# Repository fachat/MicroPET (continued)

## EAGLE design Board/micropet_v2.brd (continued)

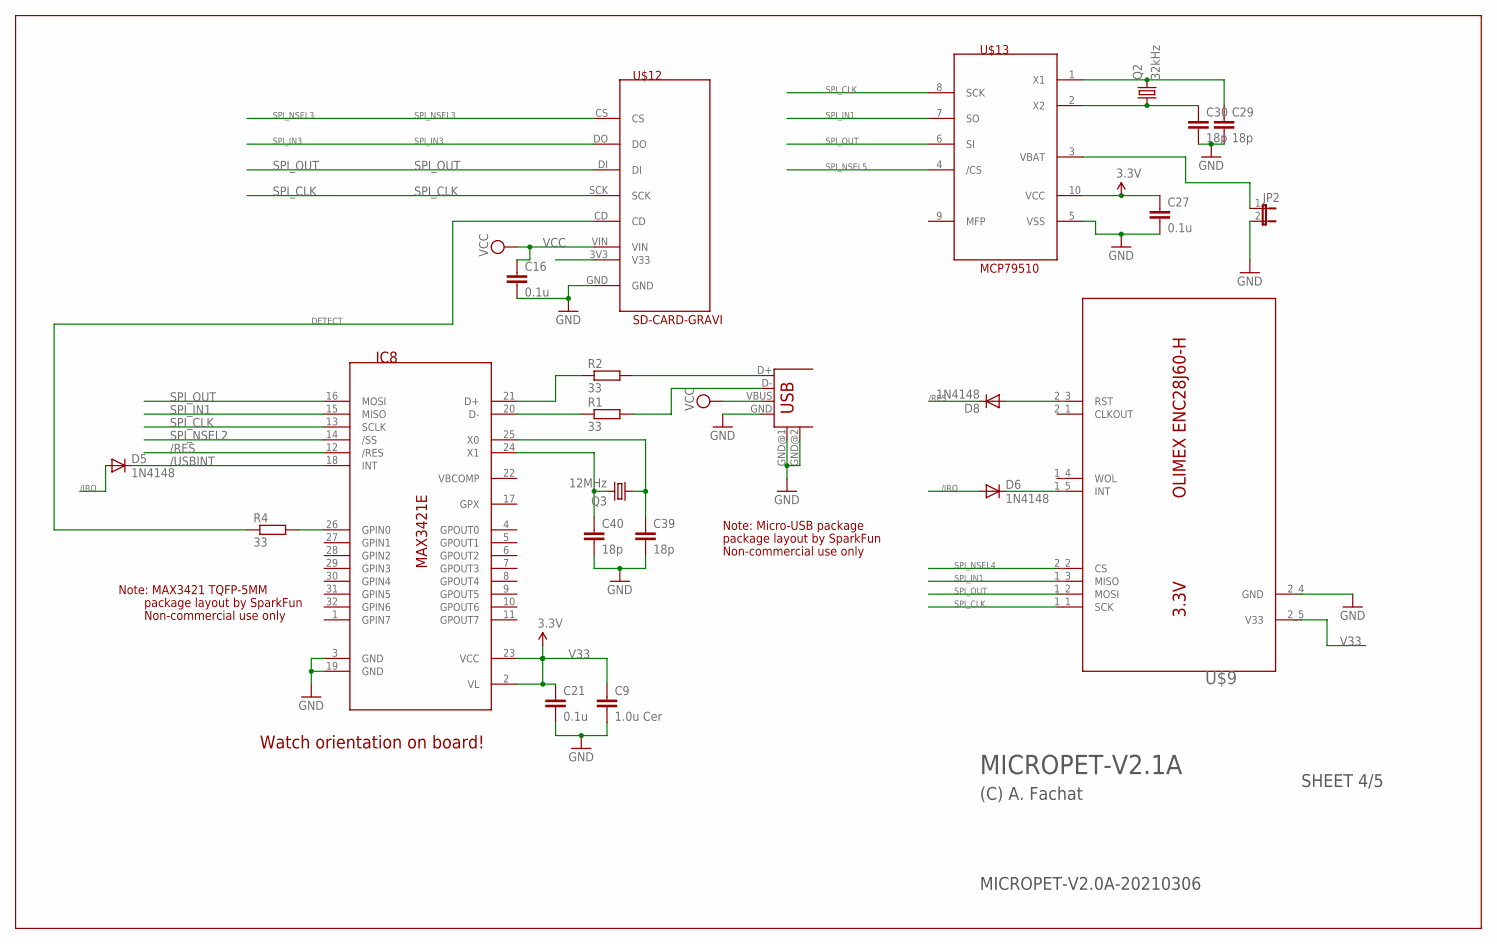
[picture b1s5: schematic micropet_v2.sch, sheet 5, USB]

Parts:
C9: 1.0u Cer; C0603
C16, C21, C27: 0.1u; C0603
C29, C30, C39, C40: 18p; C0603
D5, D6, D8: 1N4148; D-5
IC8: MAX3421E; TQFP32-5MM
JP2: JP1E; JP1
Q2: 32kHz; TC26H
Q3: 12MHz; HC49/S
R1, R2, R4: 33; 0204/7
U$9: ETHOLIENC
U$12: SD-CARD-GRAVI; GRAVITECH-SDCARD
U$13: MCP79510; MSOP10
USB1: USB-A-H

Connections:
12MHZ: C40.1, IC8.24 (X1), Q3.2
/IRQ: D5.A, D6.A; also elsewhere on the board
/RES: D8.C, IC8.12 (/RES); also elsewhere on the board
/USBINT: D5.C, IC8.18 (INT)
DETECT: R4.1, U$12.CD
FOO: U$12.3V3 (V33)
GND: C9.2, C16.2, C21.2, C27.2, C29.2, C30.2, C39.2, C40.2, IC8.3 (GND), IC8.19 (GND), JP2.2, U$9.2_4 (GND), U$12.GND, U$13.5 (VSS), USB1.GND, USB1.GND@1 (GND), USB1.GND@2 (GND); also elsewhere on the board
unnamed: IC8.20 (D-), R1.1
unnamed: IC8.21 (D+), R2.1
unnamed: JP2.1, U$13.3 (VBAT)
unnamed: C29.1, Q2.2, U$13.1 (X1)
unnamed: D6.C, U$9.1_5 (INT)
unnamed: R2.2, USB1.D+
unnamed: R1.2, USB1.D-
unnamed: IC8.26 (GPIN0), R4.2
unnamed: C30.1, Q2.1, U$13.2 (X2)
unnamed: D8.A, U$9.2_3 (RST)
unnamed: C39.1, IC8.25 (X0), Q3.1
SPI_CLK: IC8.13 (SCLK), U$9.1_1 (SCK), U$12.SCK, U$13.8 (SCK); also elsewhere on the board
SPI_IN1: IC8.15 (MISO), U$9.1_3 (MISO), U$13.7 (SO); also elsewhere on the board
SPI_IN3: U$12.DO; also elsewhere on the board
SPI_NSEL2: IC8.14 (/SS); also elsewhere on the board
SPI_NSEL3: U$12.CS; also elsewhere on the board
SPI_NSEL4: U$9.2_2 (CS); also elsewhere on the board
SPI_NSEL5: U$13.4 (/CS); also elsewhere on the board
SPI_OUT: IC8.16 (MOSI), U$9.1_2 (MOSI), U$12.DI, U$13.6 (SI); also elsewhere on the board
V33: C9.1, C21.1, C27.1, IC8.2 (VL), IC8.23 (VCC), U$9.2_5 (V33), U$13.10 (VCC); also elsewhere on the board
VCC: C16.1, U$12.VIN, USB1.VBUS; also elsewhere on the board

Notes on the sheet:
Watch orientation on board!
Note: MAX3421 TQFP-5MM
Non-commercial use only
package layout by SparkFun
MICROPET-V2.0A-20210306
MICROPET-V2.1A
(C) A. Fachat
SHEET 4/5
Note: Micro-USB package

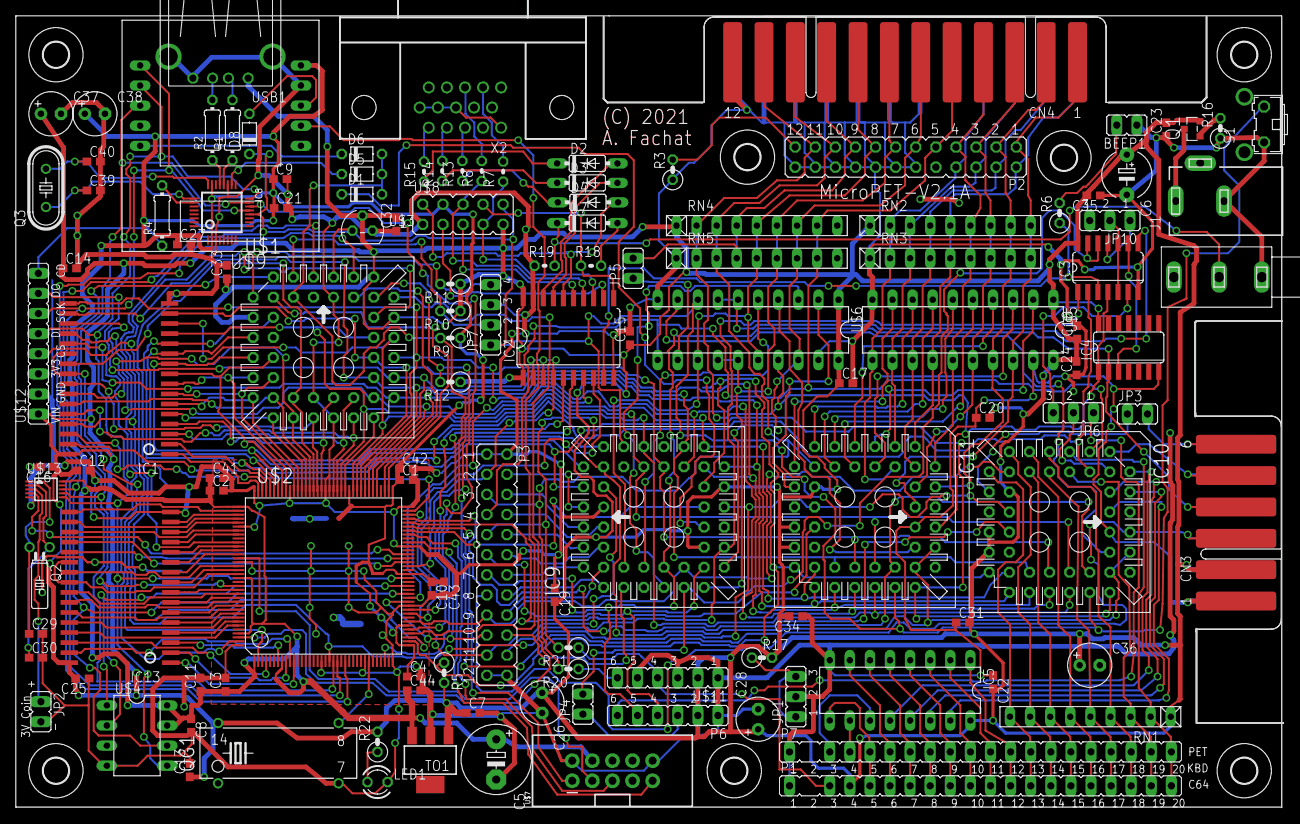
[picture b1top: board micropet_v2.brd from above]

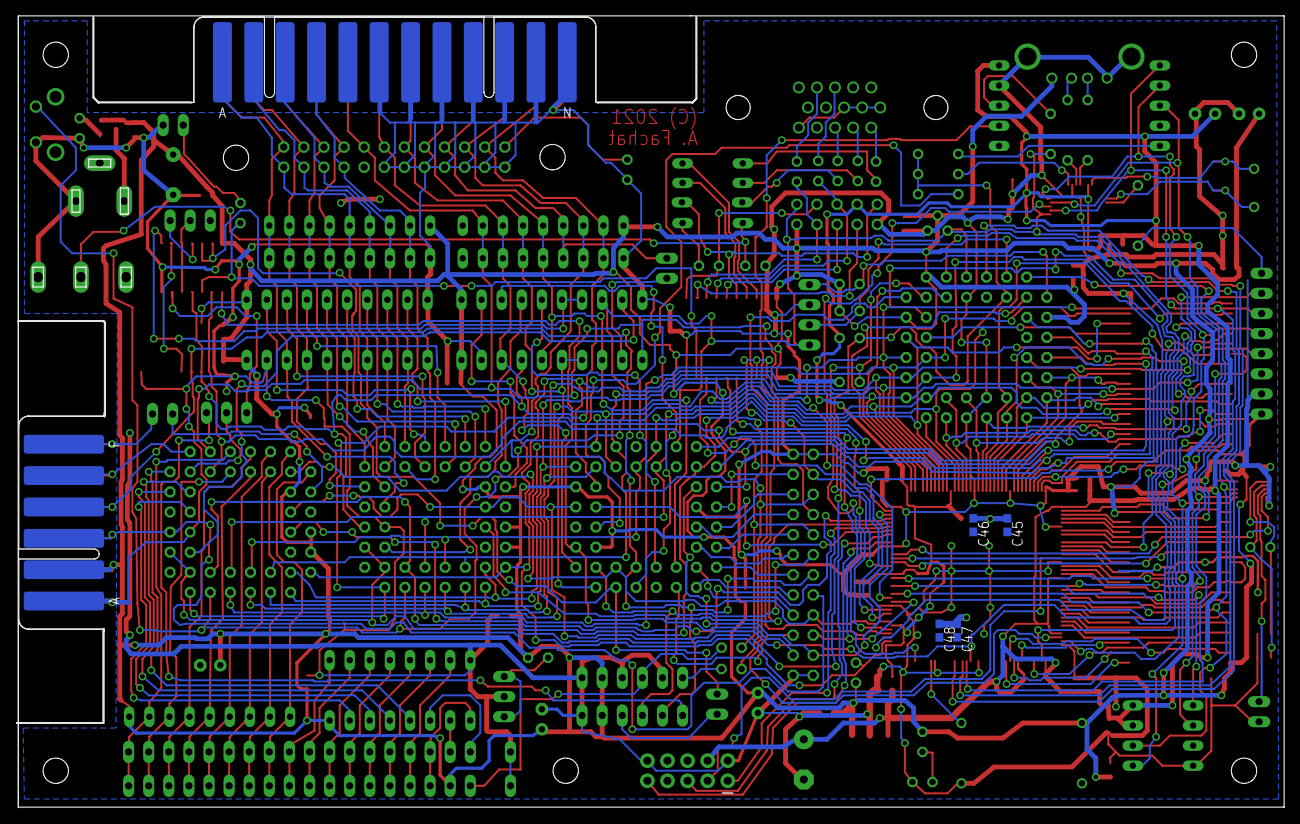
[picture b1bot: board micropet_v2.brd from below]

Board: 2 copper layers, 160.0 x 100.1 mm, 139 parts (4 on the bottom side), 217 nets.

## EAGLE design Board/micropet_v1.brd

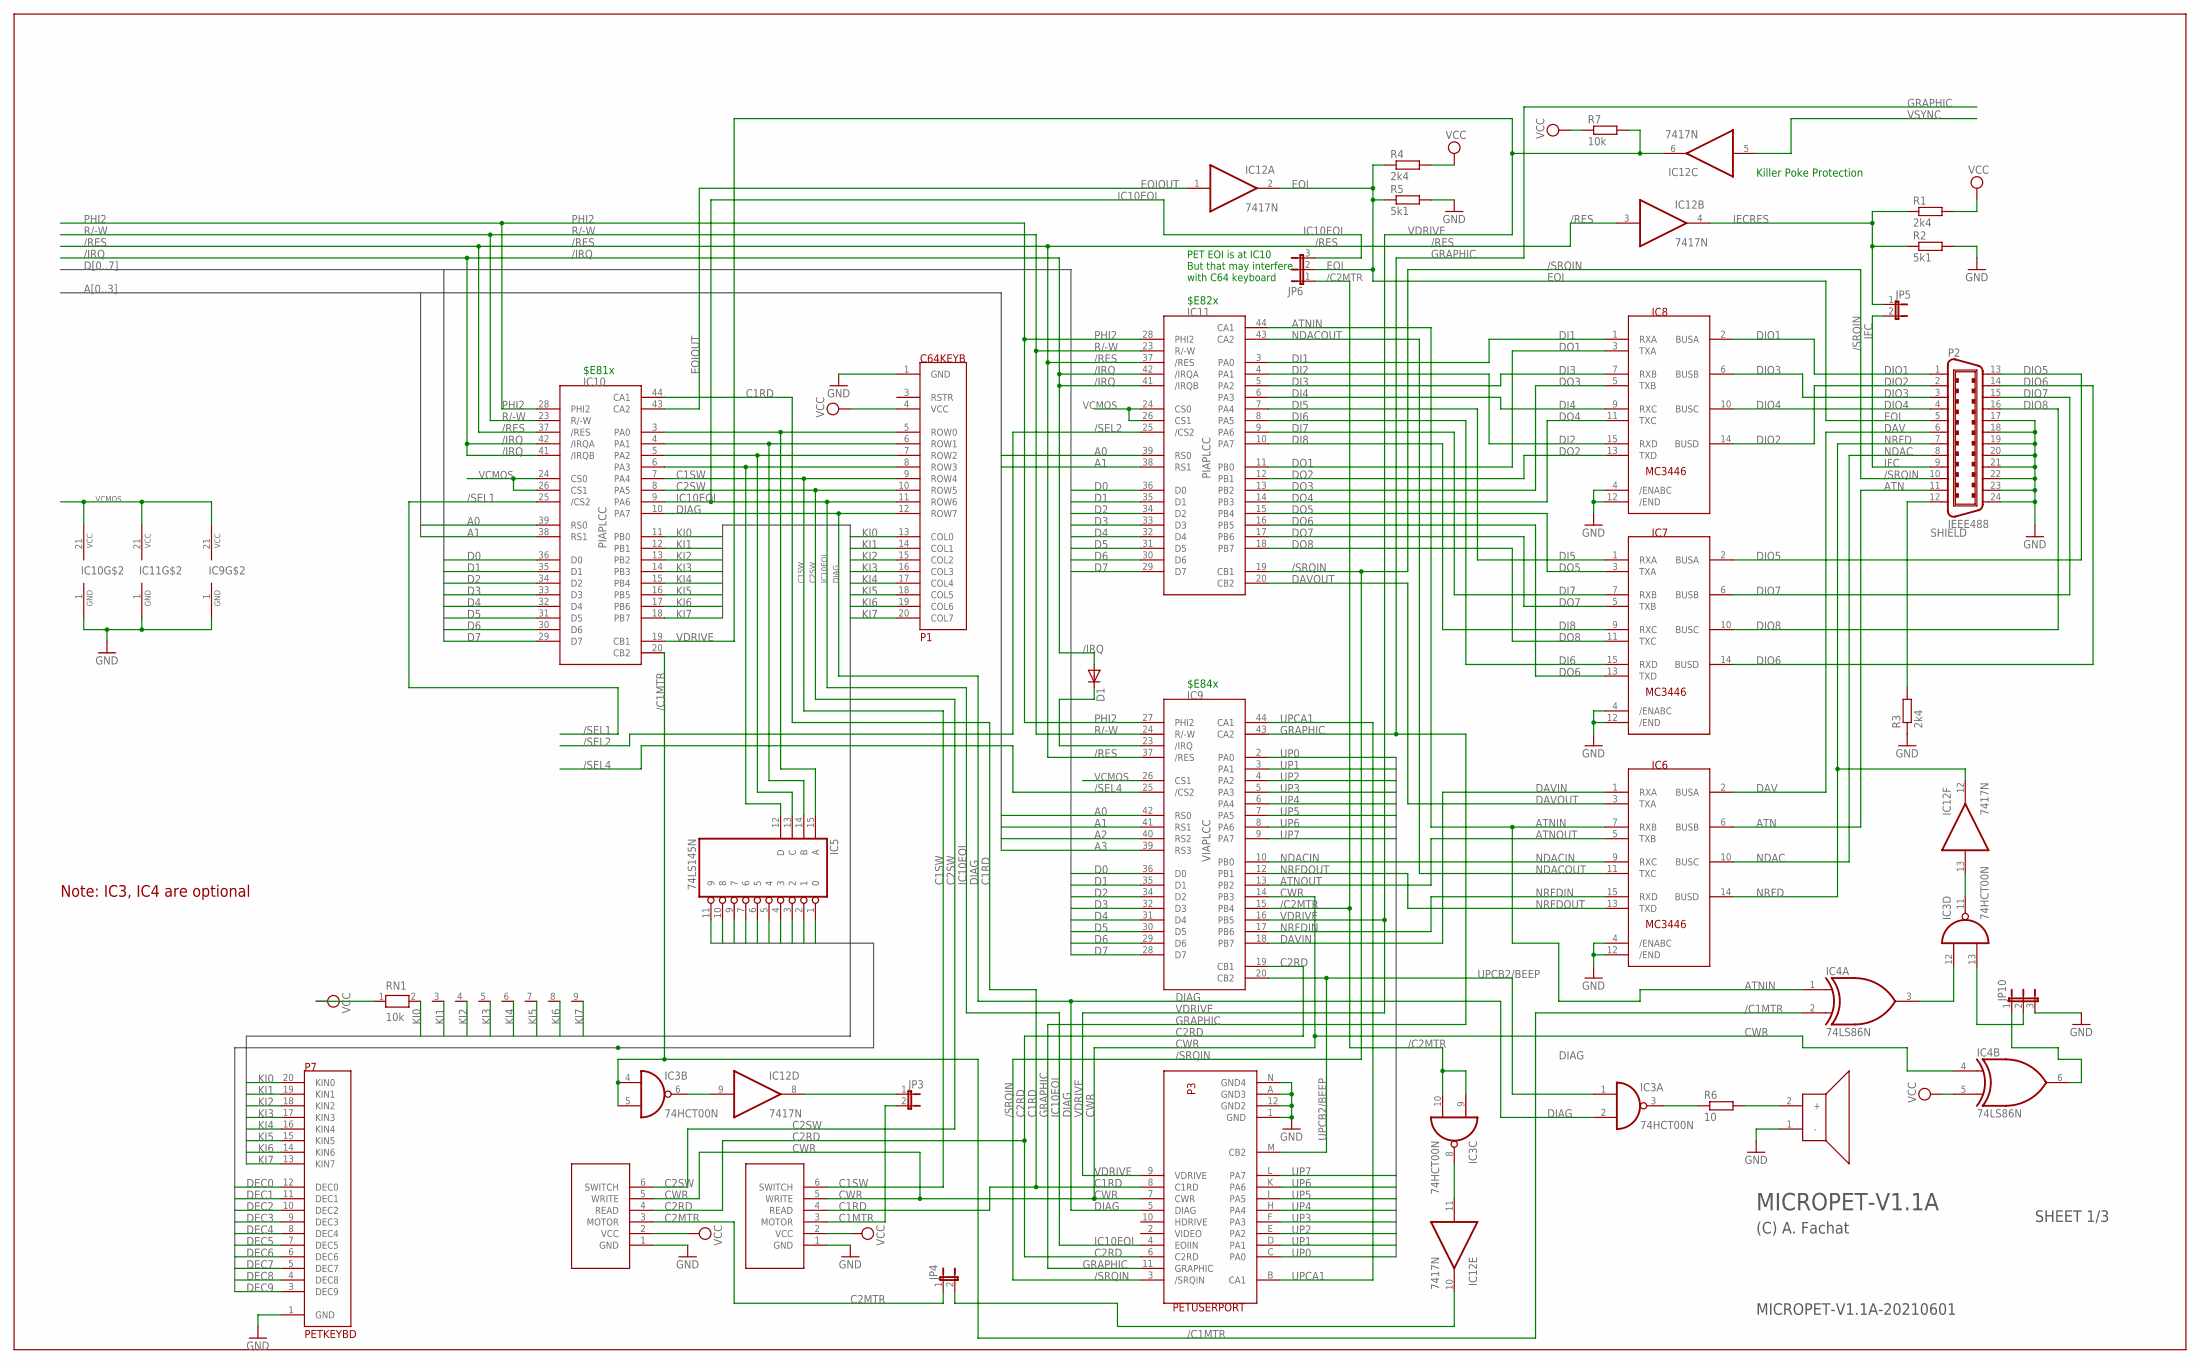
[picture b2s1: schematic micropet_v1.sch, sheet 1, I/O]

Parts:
BEEP1: PIEZOBEEPER; JP2
D1: DIODE-D-5; D-5
IC3: 74HCT00N; DIL14
IC4: 74LS86N; DIL14
IC5: 74LS145N; DIL16
IC6, IC7, IC8: MC3446; DIL16
IC9: VIAPLCC; PLCC44
IC10, IC11: PIAPLCC; PLCC44
IC12: 7417N; DIL14
JP3, JP4, JP5: JP1E; JP1
JP6, JP10: JP2E; JP2
P1: C64KEYB
P2: IEEE488; 24HP
P3: PETUSERPORT; FLAT24
P5, P6: CBMTAPE; JP6
P7: PETKEYBD; C64KEYB
R1, R3: 2k4; 0207/2V
R2, R5: 5k1; 0207/2V
R4: 2k4; 0207/10
R6: 10; 0207/2V
R7: 10k; 0207/10
RN1: 10k; RN-9

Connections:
/C1MTR: IC3.4 (I0), IC3.5 (I1), IC4.2 (I1), IC10.20 (CB2)
/C2MTR: IC3.9 (I0), IC3.10 (I1), IC9.15 (PB4), JP6.1
/IRQ: D1.A, IC10.41 (/IRQB), IC10.42 (/IRQA), IC11.41 (/IRQB), IC11.42 (/IRQA); also elsewhere on the board
/RES: IC9.37 (/RES), IC10.37 (/RES), IC11.37 (/RES), IC12.3 (I); also elsewhere on the board
/SEL1: IC10.25 (/CS2); also elsewhere on the board
/SEL2: IC11.25 (/CS2); also elsewhere on the board
/SEL4: IC9.25 (/CS2); also elsewhere on the board
/SRQIN: IC11.19 (CB1), P2.10, P3.3 (/SRQIN)
A0: IC9.42 (RS0), IC10.39 (RS0), IC11.39 (RS0); also elsewhere on the board
A1: IC9.41 (RS1), IC10.38 (RS1), IC11.38 (RS1); also elsewhere on the board
A2: IC9.40 (RS2); also elsewhere on the board
A3: IC9.39 (RS3); also elsewhere on the board
ATN: IC6.6 (BUSB), P2.11
ATNIN: IC4.1 (I0), IC6.7 (RXB), IC11.44 (CA1)
ATNOUT: IC6.5 (TXB), IC9.13 (PB2)
C1MTR: JP3.2, P5.3 (MOTOR)
C1RD: IC10.44 (CA1), P3.8 (C1RD), P5.4 (READ)
C1SW: IC10.7 (PA4), P1.9 (ROW4), P5.6 (SWITCH)
C2MTR: JP4.1, P6.3 (MOTOR)
C2RD: IC9.19 (CB1), P3.6 (C2RD), P6.4 (READ)
C2SW: IC10.8 (PA5), P1.10 (ROW5), P6.6 (SWITCH)
CWR: IC4.4 (I0), IC9.14 (PB3), P3.7 (CWR), P5.5 (WRITE), P6.5 (WRITE)
D0: IC9.36 (D0), IC10.36 (D0), IC11.36 (D0); also elsewhere on the board
D1: IC9.35 (D1), IC10.35 (D1), IC11.35 (D1); also elsewhere on the board
D2: IC9.34 (D2), IC10.34 (D2), IC11.34 (D2); also elsewhere on the board
D3: IC9.32 (D3), IC10.33 (D3), IC11.33 (D3); also elsewhere on the board
D4: IC9.31 (D4), IC10.32 (D4), IC11.32 (D4); also elsewhere on the board
D5: IC9.30 (D5), IC10.31 (D5), IC11.31 (D5); also elsewhere on the board
D6: IC9.29 (D6), IC10.30 (D6), IC11.30 (D6); also elsewhere on the board
D7: IC9.28 (D7), IC10.29 (D7), IC11.29 (D7); also elsewhere on the board
DAV: IC6.2 (BUSA), P2.6
DAVIN: IC6.1 (RXA), IC9.18 (PB7)
DAVOUT: IC6.3 (TXA), IC11.20 (CB2)
DEC0: IC5.1 (0), P7.12 (DEC0)
DEC1: IC5.2 (1), P7.11 (DEC1)
DEC2: IC5.3 (2), P7.10 (DEC2)
DEC3: IC5.4 (3), P7.9 (DEC3)
DEC4: IC5.5 (4), P7.8 (DEC4)
DEC5: IC5.6 (5), P7.7 (DEC5)
DEC6: IC5.7 (6), P7.6 (DEC6)
DEC7: IC5.9 (7), P7.5 (DEC7)
DEC8: IC5.10 (8), P7.4 (DEC8)
DEC9: IC5.11 (9), P7.3 (DEC9)
DI1: IC8.1 (RXA), IC11.3 (PA0)
DI2: IC8.15 (RXD), IC11.4 (PA1)
DI3: IC8.7 (RXB), IC11.5 (PA2)
DI4: IC8.9 (RXC), IC11.6 (PA3)
DI5: IC7.1 (RXA), IC11.7 (PA4)
DI6: IC7.15 (RXD), IC11.8 (PA5)
DI7: IC7.7 (RXB), IC11.9 (PA6)
DI8: IC7.9 (RXC), IC11.10 (PA7)
DIAG: IC3.2 (I1), IC10.10 (PA7), P1.12 (ROW7), P3.5 (DIAG)
DIO1: IC8.2 (BUSA), P2.1
DIO2: IC8.14 (BUSD), P2.2
DIO3: IC8.6 (BUSB), P2.3
DIO4: IC8.10 (BUSC), P2.4
DIO5: IC7.2 (BUSA), P2.13
DIO6: IC7.14 (BUSD), P2.14
DIO7: IC7.6 (BUSB), P2.15
DIO8: IC7.10 (BUSC), P2.16
DO1: IC8.3 (TXA), IC11.11 (PB0)
DO2: IC8.13 (TXD), IC11.12 (PB1)
DO3: IC8.5 (TXB), IC11.13 (PB2)
DO4: IC8.11 (TXC), IC11.14 (PB3)
DO5: IC7.3 (TXA), IC11.15 (PB4)
DO6: IC7.13 (TXD), IC11.16 (PB5)
DO7: IC7.5 (TXB), IC11.17 (PB6)
DO8: IC7.11 (TXC), IC11.18 (PB7)
EOI: IC12.2 (O), JP6.2, P2.5, R4.1, R5.1
EOIOUT: IC10.43 (CA2), IC12.1 (I)
GND: BEEP1.1 (-), IC3.7 (GND), IC4.7 (GND), IC5.8 (GND), IC6.4 (/ENABC), IC6.8 (GND), IC6.12 (/END), IC7.4 (/ENABC), IC7.8 (GND), IC7.12 (/END), IC8.4 (/ENABC), IC8.8 (GND), IC8.12 (/END), IC9.1 (GND), IC10.1 (GND), IC11.1 (GND), IC12.7 (GND), JP10.3, P1.1 (GND), P2.17, P2.18, P2.19, P2.20, P2.21, P2.22, P2.23, P2.24, P3.1 (GND), P3.12 (GND2), P3.A (GND3), P3.N (GND4), P5.1 (GND), P6.1 (GND), P7.1 (GND), R2.2, R3.1, R5.2; also elsewhere on the board
GRAPHIC: IC9.43 (CA2), P3.11 (GRAPHIC); also elsewhere on the board
IC10EOI: IC10.9 (PA6), JP6.3, P1.11 (ROW6), P3.4 (EOIIN)
IECRES: IC12.4 (O), JP5.1, R1.1, R2.1
IFC: JP5.2, P2.9
KI0: IC10.11 (PB0), P1.13 (COL0), P7.20 (KIN0), RN1.2
KI1: IC10.12 (PB1), P1.14 (COL1), P7.19 (KIN1), RN1.3
KI2: IC10.13 (PB2), P1.15 (COL2), P7.18 (KIN2), RN1.4
KI3: IC10.14 (PB3), P1.16 (COL3), P7.17 (KIN3), RN1.5
KI4: IC10.15 (PB4), P1.17 (COL4), P7.16 (KIN4), RN1.6
KI5: IC10.16 (PB5), P1.18 (COL5), P7.15 (KIN5), RN1.7
KI6: IC10.17 (PB6), P1.19 (COL6), P7.14 (KIN6), RN1.8
KI7: IC10.18 (PB7), P1.20 (COL7), P7.13 (KIN7), RN1.9
unnamed: IC3.12 (I0), IC4.3 (O)
unnamed: IC3.13 (I1), JP10.2
unnamed: IC3.3 (O), R6.1
unnamed: BEEP1.2 (+), R6.2
unnamed: D1.C, IC9.23 (/IRQ)
unnamed: IC3.11 (O), IC12.13 (I)
unnamed: IC3.6 (O), IC12.9 (I)
unnamed: IC12.8 (O), JP3.1
unnamed: IC12.10 (O), JP4.2
unnamed: IC5.15 (A), IC10.3 (PA0), P1.5 (ROW0)
unnamed: IC5.14 (B), IC10.4 (PA1), P1.6 (ROW1)
unnamed: IC5.13 (C), IC10.5 (PA2), P1.7 (ROW2)
unnamed: IC5.12 (D), IC10.6 (PA3), P1.8 (ROW3)
unnamed: IC3.8 (O), IC12.11 (I)
unnamed: IC4.6 (O), JP10.1
NDAC: IC6.10 (BUSC), P2.8
NDACIN: IC6.9 (RXC), IC9.10 (PB0)
NDACOUT: IC6.11 (TXC), IC11.43 (CA2)
NRFD: IC6.14 (BUSD), IC12.12 (O), P2.7
NRFDIN: IC6.15 (RXD), IC9.17 (PB6)
NRFDOUT: IC6.13 (TXD), IC9.12 (PB1)
R/-W: IC9.24 (R/-W), IC10.23 (R/-W), IC11.23 (R/-W); also elsewhere on the board
SHIELD: P2.12, R3.2
UP0: IC9.2 (PA0), P3.C (PA0)
UP1: IC9.3 (PA1), P3.D (PA1)
UP2: IC9.4 (PA2), P3.E (PA2)
UP3: IC9.5 (PA3), P3.F (PA3)
UP4: IC9.6 (PA4), P3.H (PA4)
UP5: IC9.7 (PA5), P3.J (PA5)
UP6: IC9.8 (PA6), P3.K (PA6)
UP7: IC9.9 (PA7), P3.L (PA7)
UPCA1: IC9.44 (CA1), P3.B (CA1)
UPCB2/BEEP: IC3.1 (I0), IC9.20 (CB2), P3.M (CB2)
VCC: IC3.14 (VCC), IC4.5 (I1), IC4.14 (VCC), IC5.16 (VCC), IC6.16 (VCC), IC7.16 (VCC), IC8.16 (VCC), IC12.14 (VCC), P1.4 (VCC), P5.2 (VCC), P6.2 (VCC), R1.2, R4.2, R7.1, RN1.1; also elsewhere on the board
VCMOS: IC9.21 (VCC), IC9.26 (CS1), IC10.21 (VCC), IC10.24 (CS0), IC10.26 (CS1), IC11.21 (VCC), IC11.24 (CS0), IC11.26 (CS1); also elsewhere on the board
VDRIVE: IC9.16 (PB5), IC10.19 (CB1), IC12.6 (O), P3.9 (VDRIVE), R7.2
VSYNC: IC12.5 (I); also elsewhere on the board

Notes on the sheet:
MICROPET-V1.1A-20210601
MICROPET-V1.1A
(C) A. Fachat
Killer Poke Protection
$E82x
$E84x
$E81x
PET EOI is at IC10 But that may interfere with C64 keyboard
SHEET 1/3
Note: IC3, IC4 are optional

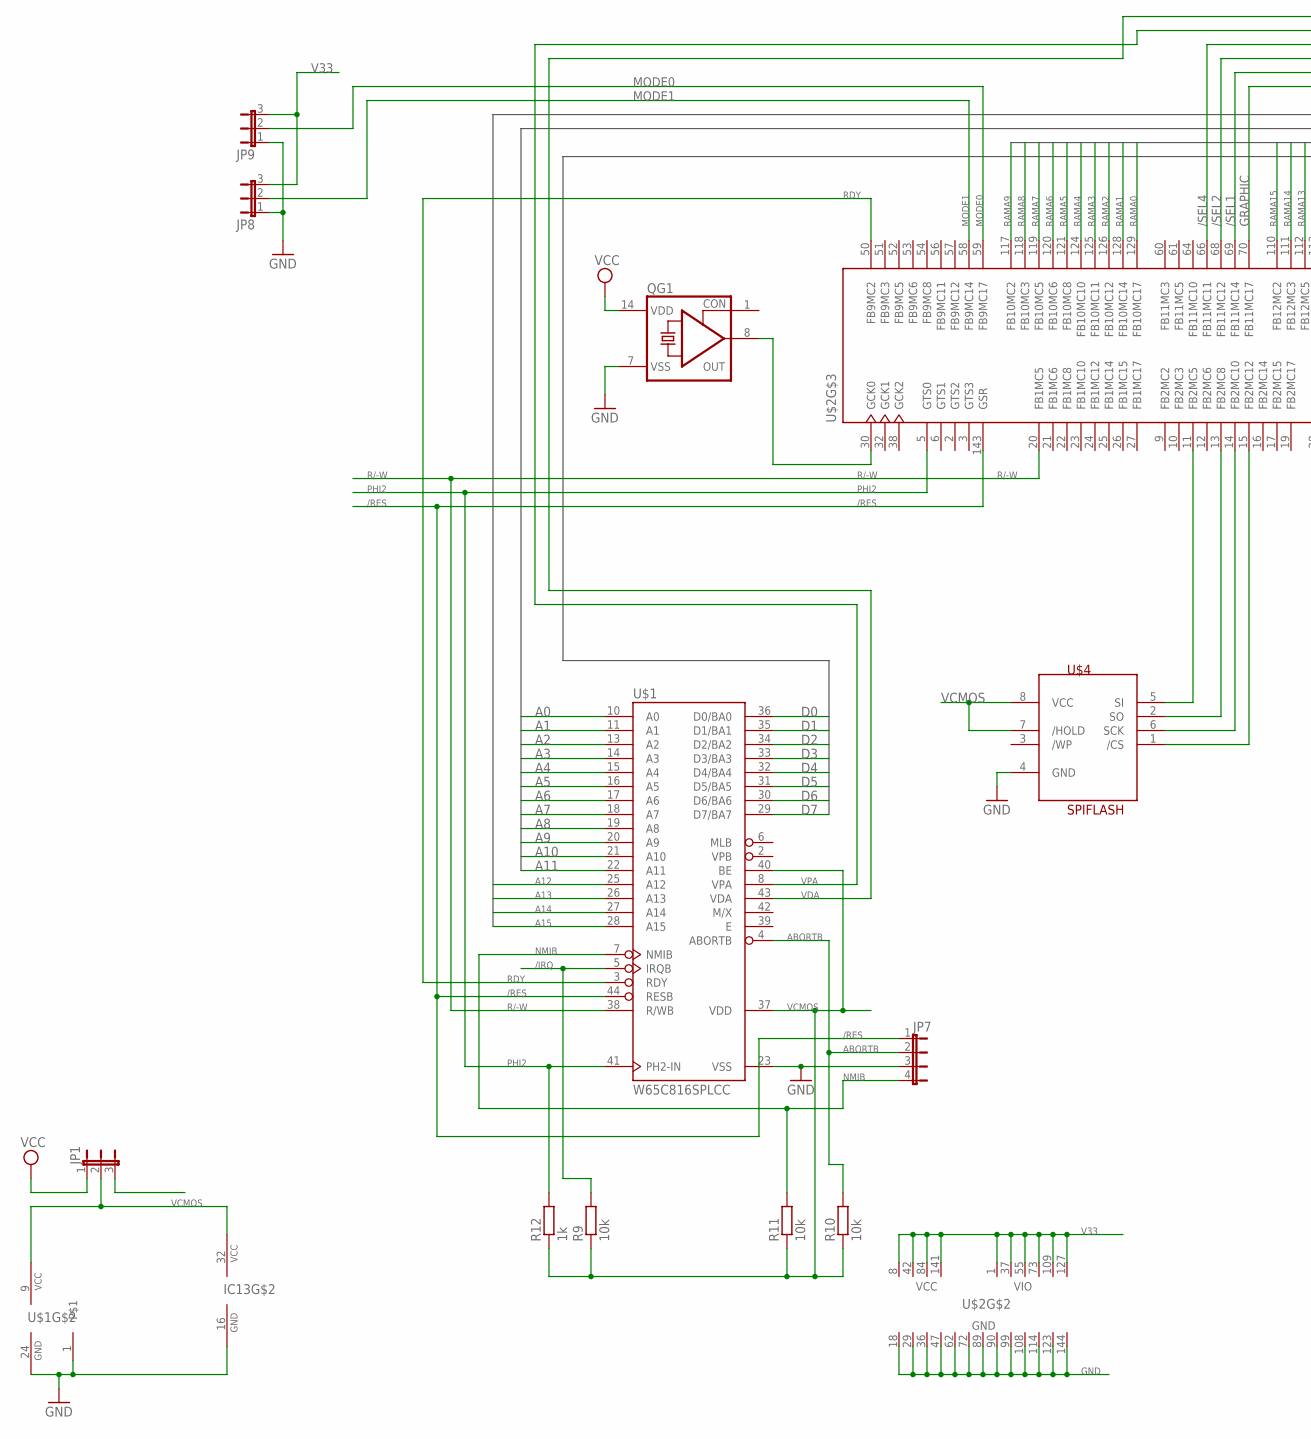
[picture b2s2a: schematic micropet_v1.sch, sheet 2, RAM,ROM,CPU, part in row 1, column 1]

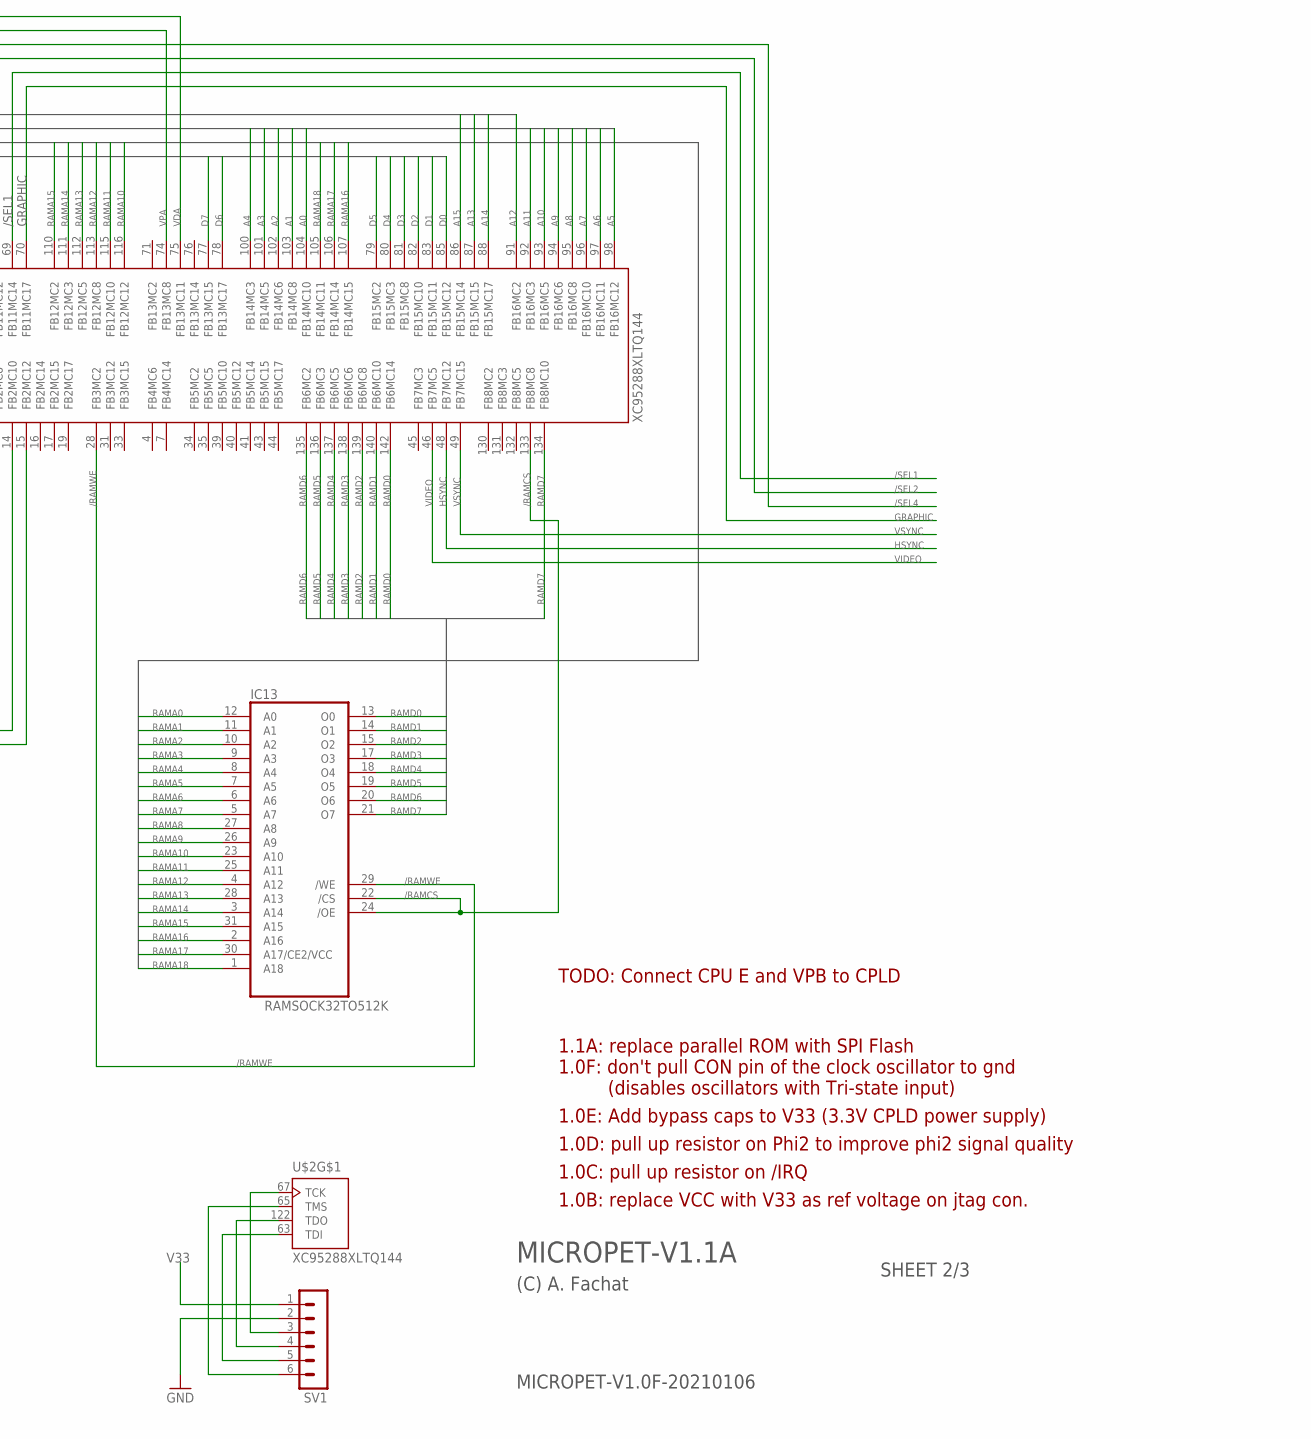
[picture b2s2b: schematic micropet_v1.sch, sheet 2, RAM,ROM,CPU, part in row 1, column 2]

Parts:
IC13: RAMSOCK32TO512K; DIL32OPT28
JP1, JP8, JP9: JP2E; JP2
JP7: JP4E; JP4
QG1: CRYSTAL_RES-SG51; SG51
R9, R10, R11: 10k; 0207/2V
R12: 1k; 0207/2V
SV1: MA06-1
U$1: W65C816SPLCC; PLCC44
U$2: XC95288XLTQ144; TQFP144
U$4: SPIFLASH; DIL08

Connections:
/IRQ: R9.2, U$1.5 (IRQB); also elsewhere on the board
/RAMCS: IC13.22 (/CS), IC13.24 (/OE), U$2.133 (FB8MC8)
/RAMWE: IC13.29 (/WE), U$2.28 (FB3MC2)
/RES: JP7.1, U$1.44 (RESB), U$2.143 (GSR); also elsewhere on the board
/SEL1: U$2.69 (FB11MC14); also elsewhere on the board
/SEL2: U$2.68 (FB11MC12); also elsewhere on the board
/SEL4: U$2.66 (FB11MC11); also elsewhere on the board
A0: U$1.10 (A0), U$2.104 (FB14MC10); also elsewhere on the board
A1: U$1.11 (A1), U$2.103 (FB14MC8); also elsewhere on the board
A2: U$1.13 (A2), U$2.102 (FB14MC6); also elsewhere on the board
A3: U$1.14 (A3), U$2.101 (FB14MC5); also elsewhere on the board
A4: U$1.15 (A4), U$2.100 (FB14MC3)
A5: U$1.16 (A5), U$2.98 (FB16MC12)
A6: U$1.17 (A6), U$2.97 (FB16MC11)
A7: U$1.18 (A7), U$2.96 (FB16MC10)
A8: U$1.19 (A8), U$2.95 (FB16MC8)
A9: U$1.20 (A9), U$2.94 (FB16MC6)
A10: U$1.21 (A10), U$2.93 (FB16MC5)
A11: U$1.22 (A11), U$2.92 (FB16MC3)
A12: U$1.25 (A12), U$2.91 (FB16MC2)
A13: U$1.26 (A13), U$2.87 (FB15MC15)
A14: U$1.27 (A14), U$2.88 (FB15MC17)
A15: U$1.28 (A15), U$2.86 (FB15MC14)
ABORTB: JP7.2, R10.2, U$1.4 (ABORTB)
D0: U$1.36 (D0/BA0), U$2.85 (FB15MC12); also elsewhere on the board
D1: U$1.35 (D1/BA1), U$2.83 (FB15MC11); also elsewhere on the board
D2: U$1.34 (D2/BA2), U$2.82 (FB15MC10); also elsewhere on the board
D3: U$1.33 (D3/BA3), U$2.81 (FB15MC8); also elsewhere on the board
D4: U$1.32 (D4/BA4), U$2.80 (FB15MC3); also elsewhere on the board
D5: U$1.31 (D5/BA5), U$2.79 (FB15MC2); also elsewhere on the board
D6: U$1.30 (D6/BA6), U$2.78 (FB13MC17); also elsewhere on the board
D7: U$1.29 (D7/BA7), U$2.77 (FB13MC15); also elsewhere on the board
GND: IC13.16 (GND), JP7.3, JP8.1, JP9.1, QG1.7 (VSS), SV1.2, U$1.1, U$1.23 (VSS), U$1.24 (GND), U$2.18 (GND), U$2.29 (GND), U$2.36 (GND), U$2.47 (GND), U$2.62 (GND), U$2.72 (GND), U$2.89 (GND), U$2.90 (GND), U$2.99 (GND), U$2.108 (GND), U$2.114 (GND), U$2.123 (GND), U$2.144 (GND), U$4.4 (GND); also elsewhere on the board
GRAPHIC: U$2.70 (FB11MC17); also elsewhere on the board
HSYNC: U$2.48 (FB7MC12); also elsewhere on the board
MODE0: JP9.2, U$2.59 (FB9MC17)
unnamed: QG1.8 (OUT), U$2.30 (GCK0)
unnamed: U$2.15 (FB2MC12), U$4.1 (/CS)
unnamed: U$2.14 (FB2MC10), U$4.6 (SCK)
unnamed: U$2.13 (FB2MC8), U$4.2 (SO)
unnamed: U$2.11 (FB2MC5), U$4.5 (SI)
NMIB: JP7.4, R11.2, U$1.7 (NMIB)
PHI2: R12.2, U$1.41 (PH2-IN), U$2.5 (GTS0)
R/-W: U$1.38 (R/WB), U$2.20 (FB1MC5); also elsewhere on the board
RAMA0: IC13.12 (A0), U$2.129 (FB10MC17)
RAMA1: IC13.11 (A1), U$2.128 (FB10MC14)
RAMA2: IC13.10 (A2), U$2.126 (FB10MC12)
RAMA3: IC13.9 (A3), U$2.125 (FB10MC11)
RAMA4: IC13.8 (A4), U$2.124 (FB10MC10)
RAMA5: IC13.7 (A5), U$2.121 (FB10MC8)
RAMA6: IC13.6 (A6), U$2.120 (FB10MC6)
RAMA7: IC13.5 (A7), U$2.119 (FB10MC5)
RAMA8: IC13.27 (A8), U$2.118 (FB10MC3)
RAMA9: IC13.26 (A9), U$2.117 (FB10MC2)
RAMA10: IC13.23 (A10), U$2.116 (FB12MC12)
RAMA11: IC13.25 (A11), U$2.115 (FB12MC10)
RAMA12: IC13.4 (A12), U$2.113 (FB12MC8)
RAMA13: IC13.28 (A13), U$2.112 (FB12MC5)
RAMA14: IC13.3 (A14), U$2.111 (FB12MC3)
RAMA15: IC13.31 (A15), U$2.110 (FB12MC2)
RAMA16: IC13.2 (A16), U$2.107 (FB14MC15)
RAMA17: IC13.30 (A17/CE2/VCC), U$2.106 (FB14MC14)
RAMA18: IC13.1 (A18), U$2.105 (FB14MC11)
RAMD0: IC13.13 (O0), U$2.142 (FB6MC14)
RAMD1: IC13.14 (O1), U$2.140 (FB6MC10)
RAMD2: IC13.15 (O2), U$2.139 (FB6MC8)
RAMD3: IC13.17 (O3), U$2.138 (FB6MC6)
RAMD4: IC13.18 (O4), U$2.137 (FB6MC5)
RAMD5: IC13.19 (O5), U$2.136 (FB6MC3)
RAMD6: IC13.20 (O6), U$2.135 (FB6MC2)
RAMD7: IC13.21 (O7), U$2.134 (FB8MC10)
RDY: U$1.3 (RDY), U$2.50 (FB9MC2)
TCK: SV1.3, U$2.67 (TCK)
TDI: SV1.5, U$2.63 (TDI)
TDO: SV1.4, U$2.122 (TDO)
TMS: SV1.6, U$2.65 (TMS)
V33: JP1.3, JP8.3, JP9.3, SV1.1, U$2.1 (VIO), U$2.8 (VCC), U$2.37 (VIO), U$2.42 (VCC), U$2.55 (VIO), U$2.73 (VIO), U$2.84 (VCC), U$2.109 (VIO), U$2.127 (VIO), U$2.141 (VCC); also elsewhere on the board
VCC: JP1.1, QG1.14 (VDD); also elsewhere on the board
VCMOS: IC13.32 (VCC), JP1.2, R9.1, R10.1, R11.1, R12.1, U$1.9 (VCC), U$1.37 (VDD), U$1.40 (BE), U$4.7 (/HOLD), U$4.8 (VCC); also elsewhere on the board
VDA: U$1.43 (VDA), U$2.75 (FB13MC11)
VIDEO: U$2.46 (FB7MC5); also elsewhere on the board
VPA: U$1.8 (VPA), U$2.74 (FB13MC8)
VSYNC: U$2.49 (FB7MC15); also elsewhere on the board

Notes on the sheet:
MICROPET-V1.0F-20210106
MICROPET-V1.1A
(C) A. Fachat
SHEET 2/3
1.0B: replace VCC with V33 as ref voltage on jtag con.
1.0C: pull up resistor on /IRQ
1.0D: pull up resistor on Phi2 to improve phi2 signal quality
1.0E: Add bypass caps to V33 (3.3V CPLD power supply)
TODO: Connect CPU E and VPB to CPLD
1.0F: don't pull CON pin of the clock oscillator to gnd (disables oscillators with Tri-state input)
1.1A: replace parallel ROM with SPI Flash

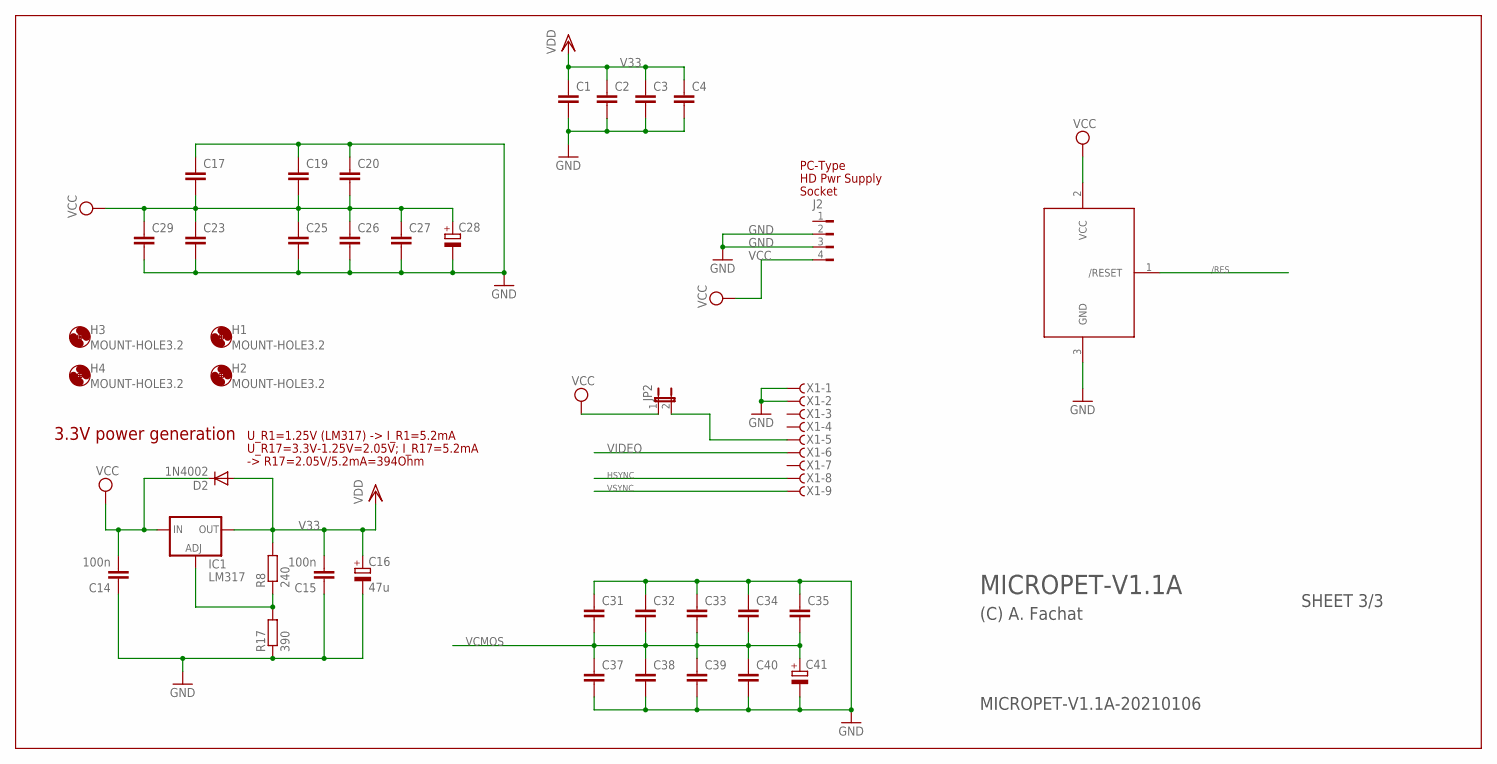
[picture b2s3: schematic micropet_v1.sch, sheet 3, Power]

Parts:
C1, C2, C3, C4, C17, C19, C20, C23, C25, C26, C27, C29, C31, C32, C33, C34, C35, C37, C38, C39, C40: C-EU025-025X050; C025-025X050
C14, C15: 100n; C5B2.5
C16: 47u; E2,5-7
C28, C41: CPOL-EUE2.5-6; E2,5-6
D2: 1N4002; C1702-05
H1, H2, H3, H4: MOUNT-HOLE3.2; 3,2
IC1: LM317; 317TL
J2: FLOP-4W827001; 827001
JP2: JP1E; JP1
R8: 240; 0204/5
R17: 390; 0204/5
U$3: DS1813; TO92
X1: F09HPS; F09HP

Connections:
/RES: U$3.1 (/RESET); also elsewhere on the board
GND: C1.2, C2.2, C3.2, C4.2, C14.1, C15.1, C16.-, C17.1, C19.1, C20.1, C23.2, C25.2, C26.2, C27.2, C28.-, C29.2, C31.1, C32.1, C33.1, C34.1, C35.1, C37.2, C38.2, C39.2, C40.2, C41.-, J2.2, J2.3, R17.1, U$3.3 (GND), X1.1, X1.2; also elsewhere on the board
HSYNC: X1.8; also elsewhere on the board
unnamed: IC1.1 (ADJ), R8.1, R17.2
unnamed: JP2.2, X1.5
V33: C1.1, C2.1, C3.1, C4.1, C15.2, C16.+, D2.A, IC1.2 (OUT), R8.2; also elsewhere on the board
VCC: C14.2, C17.2, C19.2, C20.2, C23.1, C25.1, C26.1, C27.1, C28.+, C29.1, D2.C, IC1.3 (IN), J2.4, JP2.1, U$3.2 (VCC); also elsewhere on the board
VCMOS: C31.2, C32.2, C33.2, C34.2, C35.2, C37.1, C38.1, C39.1, C40.1, C41.+; also elsewhere on the board
VIDEO: X1.6; also elsewhere on the board
VSYNC: X1.9; also elsewhere on the board

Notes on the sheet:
3.3V power generation
U_R1=1.25V (LM317) -> I_R1=5.2mA
U_R17=3.3V-1.25V=2.05V; I_R17=5.2mA
-> R17=2.05V/5.2mA=394Ohm
PC-Type
HD Pwr Supply
Socket
MICROPET-V1.1A-20210106
MICROPET-V1.1A
(C) A. Fachat
SHEET 3/3

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
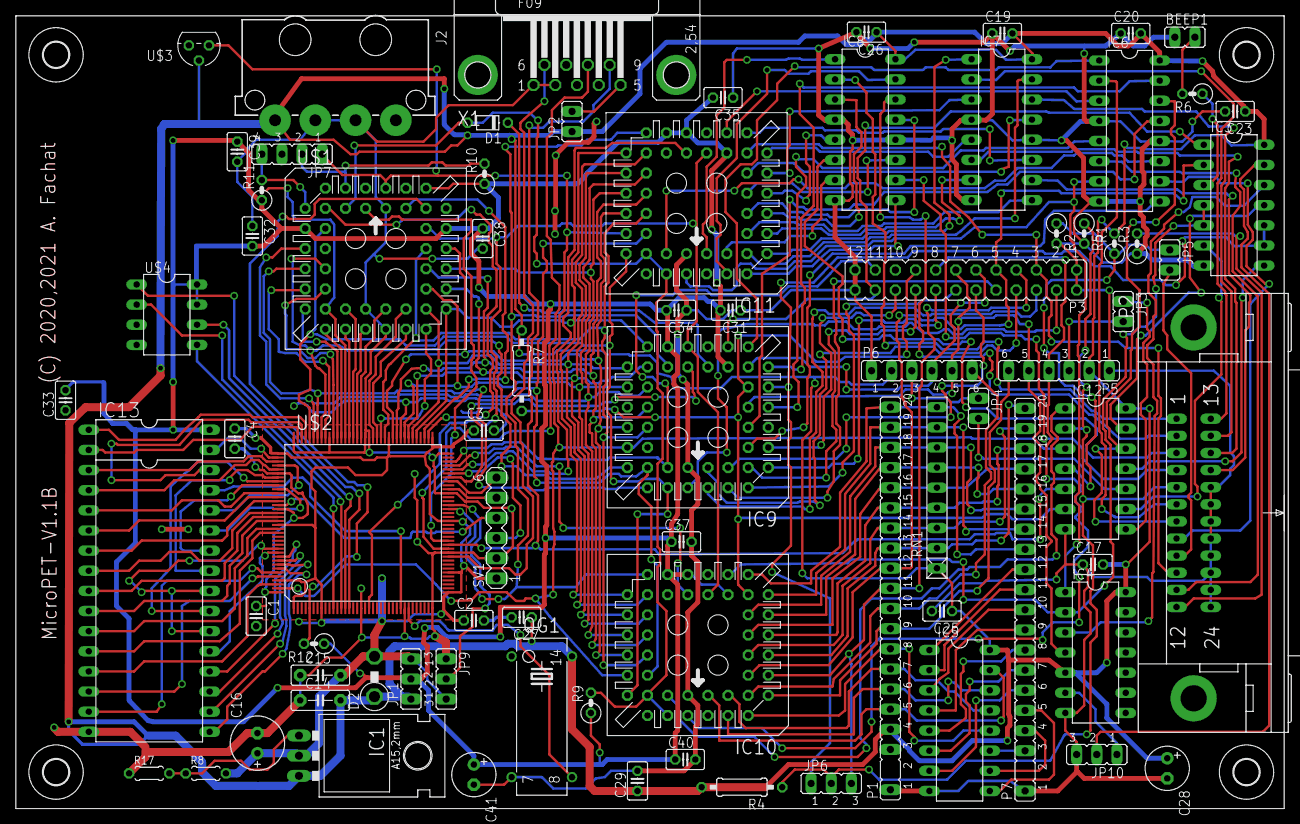
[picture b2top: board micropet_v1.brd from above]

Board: 2 copper layers, 160.0 x 100.0 mm, 82 parts (0 on the bottom side), 183 nets.

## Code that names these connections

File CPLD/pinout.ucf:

# NET VD<0>	LOC=P142 | IOSTANDARD=LVCMOS33 |PULLUP;
# NET VD<0>	LOC=P142 | IOSTANDARD=LVCMOS33 | DRIVE=16;

NET VD<0>	LOC=P116;
NET VD<1>	LOC=P113;
NET VD<2>	LOC=P111;
NET VD<3>	LOC=P110;
NET VD<4>	LOC=P112;
NET VD<5>	LOC=P115;
NET VD<6>	LOC=P58;
NET VD<7>	LOC=P59;

NET VA<0>	LOC=P119;
NET VA<1>	LOC=P120;
NET VA<2>	LOC=P121;
NET VA<3>	LOC=P125;
NET VA<4>	LOC=P130;	#P126;
NET VA<5>	LOC=P131;	# actually P132, P131 is VA11
NET VA<6>	LOC=P133;	# actually P134, P133 is VA9
NET VA<7>	LOC=P136;
NET VA<8>	LOC=P135;
NET VA<9>	LOC=P132;	# actually P133, P132 is VA5
NET VA<10>	LOC=P124;
NET VA<11>	LOC=P134;	# actually P131, P134 is VA6
NET VA<12>	LOC=P138;
NET VA<13>	LOC=P137;
NET VA<14>	LOC=P7;
NET VA<15>	LOC=P10;
NET VA<16>	LOC=P9;
NET VA<17>	LOC=P4;
NET VA<18>	LOC=P11;

NET FA<15>	LOC=P71;
NET FA<16>	LOC=P105;
NET FA<17>	LOC=P106;
NET FA<18>	LOC=P107;

NET D<0>	LOC=P86;
NET D<1>	LOC=P83;
NET D<2>	LOC=P82;
NET D<3>	LOC=P81;
NET D<4>	LOC=P80;
NET D<5>	LOC=P79;
NET D<6>	LOC=P78;
NET D<7>	LOC=P77;

NET A<0>	LOC=P104;
NET A<1>	LOC=P103;
NET A<2>	LOC=P102;
NET A<3>	LOC=P101;
NET A<4>	LOC=P100;
NET A<5>	LOC=P98;
NET A<6>	LOC=P97;
NET A<7>	LOC=P96;
NET A<8>	LOC=P95;
NET A<9>	LOC=P94;
NET A<10>	LOC=P93;
NET A<11>	LOC=P92;
NET A<12>	LOC=P91;
NET A<13>	LOC=P87;
NET A<14>	LOC=P88;
NET A<15>	LOC=P85;

NET VPA		LOC=P74;
NET VDA		LOC=P75;
	
NET NSEL1	LOC=P69;
NET NSEL2	LOC=P68;
NET NSEL4	LOC=P66;

NET NVRAMSEL	LOC=P126;
NET NFRAMSEL	LOC=P2;
NET RAMRWB	LOC=P139;

NET GRAPHIC	LOC=P70;

NET HSYNC	LOC=P48;
NET VSYNC	LOC=P49;
NET PXL 	LOC=P46; 
NET DCLK	LOC=P45;
NET DENA	LOC=P41;
NET PET_VSYNC	LOC=P43;

NET Q50M	LOC=P30;
NET Q50M	BUFG=CLK;

NET RWB		LOC=P20;
NET NRES	LOC=P143;
NET NRES	BUFG=SR;

NET PHI2_IO	LOC=P38;
NET PHI2_IO	BUFG=CLK;

#NET MLB		LOC=P21;
#NET VPB		LOC=P22;
NET E			LOC=P142;
#NET MX			LOC=P24;

NET SPI_OUT		LOC=P54;
NET SPI_CLK		LOC=P50;

NET SPI_IN1		LOC=P129;
NET SPI_IN3		LOC=P118;

NET NFLASH		LOC=P52;
NET SPI_NSEL2		LOC=P34;
NET SPI_NSEL3		LOC=P39;
NET SPI_NSEL4		LOC=P40;

NET SPI_NSEL5		LOC=P60;

NET MEMCLK		BUFG=CLK;
#NET MEMCLK		NOREDUCE;

#NET PHI2		BUFG=CLK;
NET PHI2		LOC=P57;
